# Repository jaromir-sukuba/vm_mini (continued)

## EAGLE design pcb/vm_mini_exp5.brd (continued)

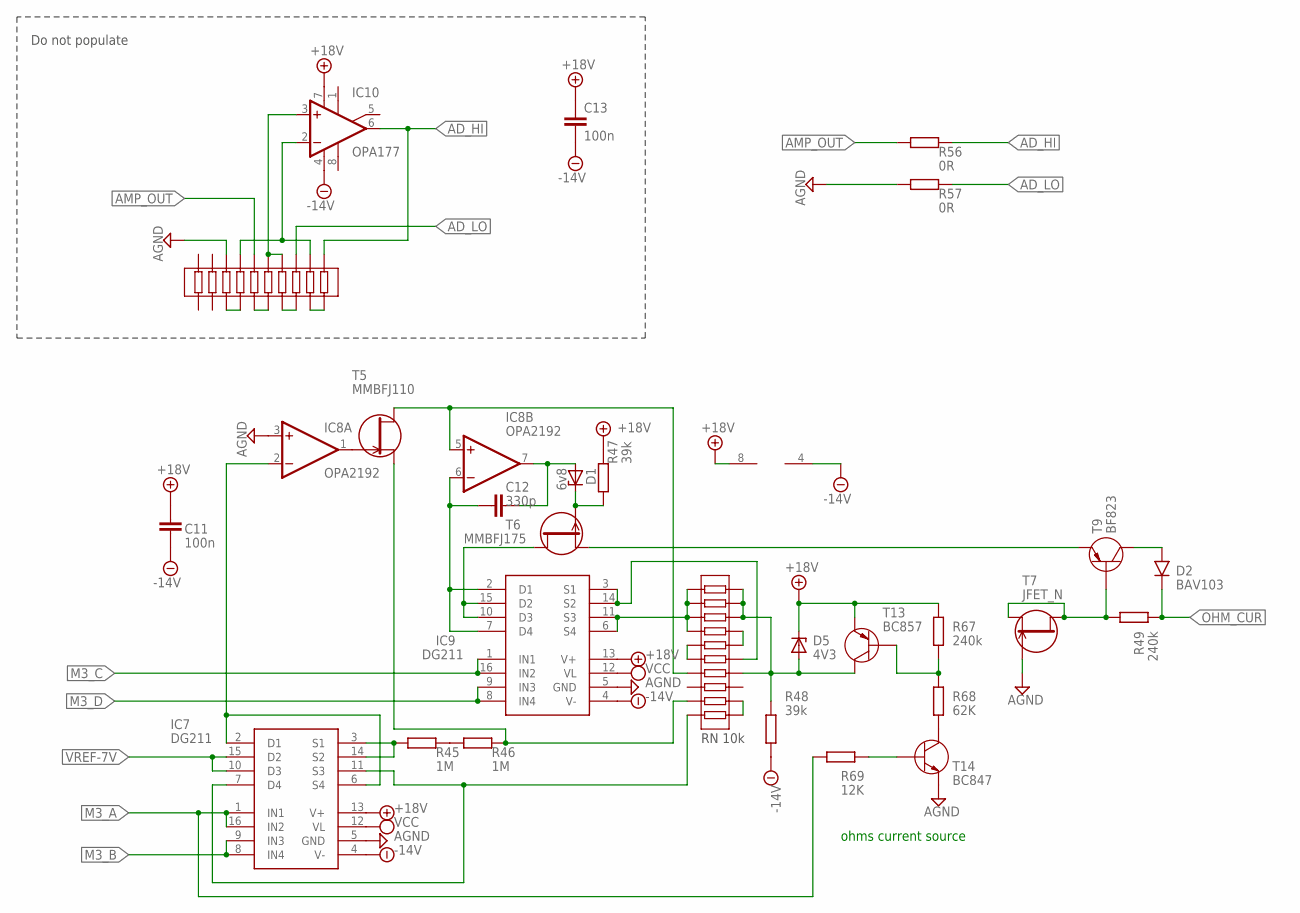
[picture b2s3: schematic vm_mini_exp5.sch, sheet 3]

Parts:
C11, C13: 100n; R0805
C12: 330p; R_MINIMELF
D1: 6v8; SOD80C
D2: BAV103; SOD-80
D5: 4V3; SOD80C
IC7, IC9: DG211; SO-16
IC8: OPA2192; SO08
IC10: OPA177; SO08
R45, R46: 1M; R_MINIMELF
R47, R48: 39k; R_MINIMELF
R49, R67: 240k; R_MINIMELF
R56, R57: 0R; R_MINIMELF
R68: 62K; R_MINIMELF
R69: 12K; R_MINIMELF
RN1, RN2: OSOP20
T5: MMBFJ110; SOT23
T6: MMBFJ175; SOT23
T7: JFET_N; SOT23
T9: BF823; SOT23
T13: BC857; SOT23
T14: BC847; SOT23

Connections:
+18V: C11.1, C13.1, D5.C, IC7.13 (V+), IC8.8 (V+), IC9.13 (V+), IC10.7 (V+), R47.P$1 (1), R67.P$2 (2), T13.2 (C); also elsewhere on the board
-14V: C11.2, C13.2, IC7.4 (V-), IC8.4 (V-), IC9.4 (V-), IC10.4 (V-), R48.P$1 (1); also elsewhere on the board
AD_HI: IC10.6 (OUT), R56.P$1 (1), RN1.1 (1A); also elsewhere on the board
AD_LO: R57.P$1 (1), RN1.3 (3A); also elsewhere on the board
AGND: IC7.5 (GND), IC8.3 (+IN), IC9.5 (GND), R57.P$2 (2), RN1.8 (8A), T7.3 (G), T14.2 (E); also elsewhere on the board
AMP_OUT: R56.P$2 (2), RN1.6 (6A); also elsewhere on the board
M3_A: IC7.1 (IN1), IC7.16 (IN2), R69.P$1 (1); also elsewhere on the board
M3_B: IC7.8 (IN4), IC7.9 (IN3); also elsewhere on the board
M3_C: IC9.1 (IN1), IC9.16 (IN2); also elsewhere on the board
M3_D: IC9.8 (IN4), IC9.9 (IN3); also elsewhere on the board
unnamed: RN1.19 (2B), RN1.20 (1B)
unnamed: IC8.5 (+IN), RN2.7 (7A), T5.1 (D)
unnamed: RN1.17 (4B), RN1.18 (3B)
unnamed: RN2.5 (5A), RN2.6 (6A)
unnamed: RN2.11 (10B), RN2.12 (9B)
unnamed: IC9.3 (S1), IC9.14 (S2), RN2.15 (6B)
unnamed: C12.P$1 (1), IC8.6 (-IN), IC9.2 (D1), IC9.7 (D4)
unnamed: IC9.6 (S4), IC9.11 (S3), RN2.1 (1A), RN2.2 (2A), RN2.3 (3A), RN2.4 (4A)
unnamed: IC7.3 (S1), IC7.14 (S2), R45.P$1 (1)
unnamed: RN2.16 (5B), RN2.17 (4B)
unnamed: IC8.1 (OUT), T5.3 (G)
unnamed: R46.P$2 (2), RN2.9 (9A), T5.2 (S)
unnamed: IC9.10 (D3), IC9.15 (D2), T6.1 (D)
unnamed: IC7.7 (D4), IC7.11 (S3), RN2.10 (10A)
unnamed: C12.P$2 (2), D1.A, IC8.7 (OUT)
unnamed: R45.P$2 (2), R46.P$1 (1)
unnamed: D1.C, R47.P$2 (2), T6.3 (G)
unnamed: IC7.2 (D1), IC7.6 (S4), IC8.2 (-IN)
unnamed: R49.P$2 (2), T7.1 (D), T7.2 (S), T9.1 (B)
unnamed: RN1.15 (6B), RN1.16 (5B)
unnamed: RN1.13 (8B), RN1.14 (7B)
unnamed: T6.2 (S), T9.2 (C)
unnamed: D2.A, T9.3 (E)
unnamed: IC10.3 (+IN), RN1.4 (4A), RN1.5 (5A)
unnamed: IC10.2 (-IN), RN1.2 (2A), RN1.7 (7A)
unnamed: D5.A, R48.P$2 (2), RN2.14 (7B), RN2.18 (3B), RN2.19 (2B), RN2.20 (1B), T13.3 (E)
unnamed: R67.P$1 (1), R68.P$1 (1), T13.1 (B)
unnamed: R68.P$2 (2), T14.3 (C)
unnamed: R69.P$2 (2), T14.1 (B)
OHM_CUR: D2.K, R49.P$1 (1); also elsewhere on the board
VCC: IC7.12 (VL), IC9.12 (VL); also elsewhere on the board
VREF-7V: IC7.10 (D3), IC7.15 (D2); also elsewhere on the board

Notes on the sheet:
Do not populate
RN 10k
ohms current source

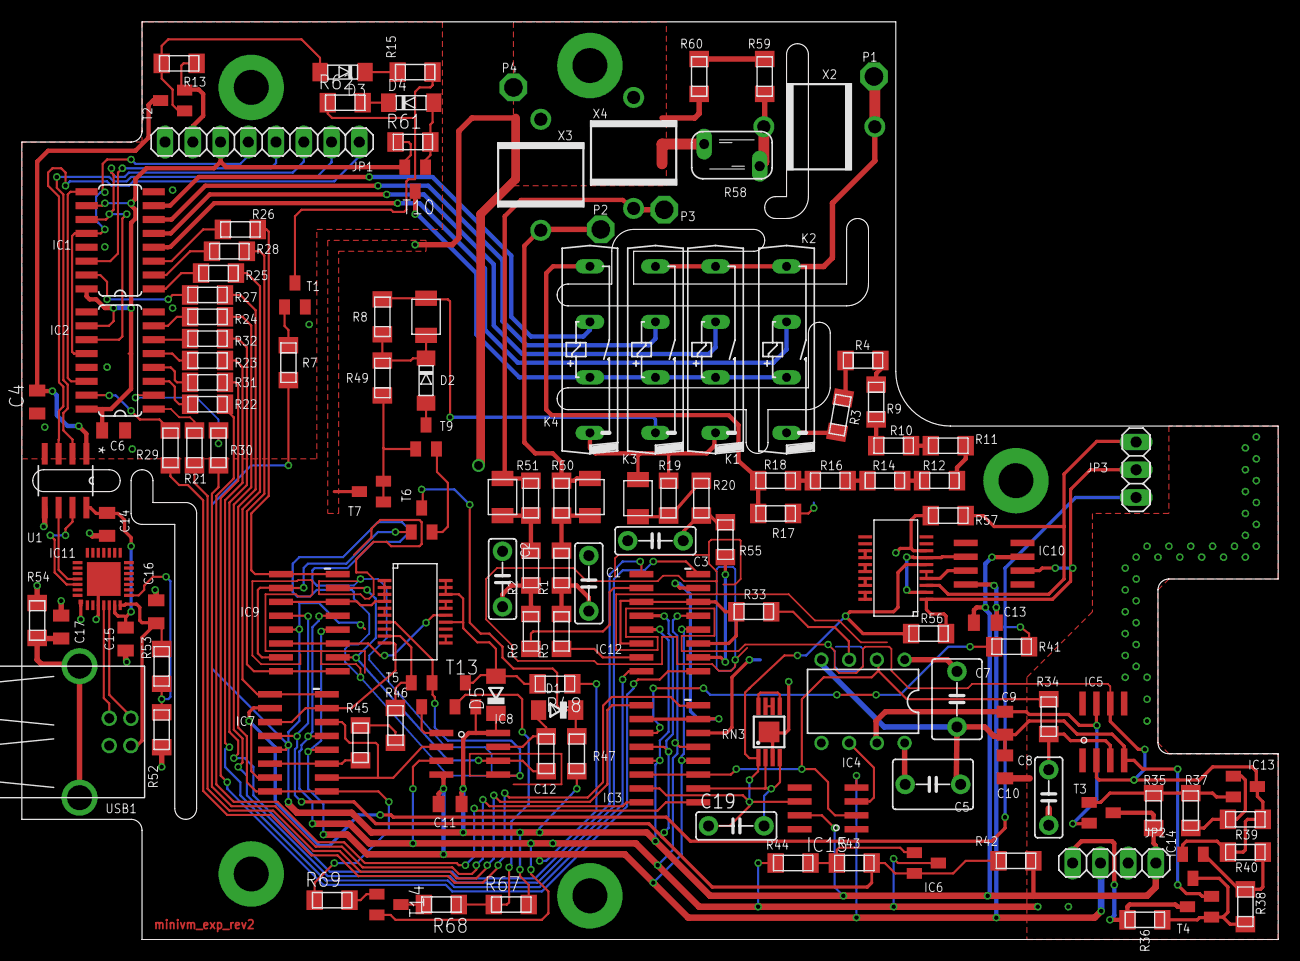
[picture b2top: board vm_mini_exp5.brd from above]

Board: 2 copper layers, 115.0 x 84.0 mm, 137 parts (0 on the bottom side), 139 nets.

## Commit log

2020-03-24 readme update
